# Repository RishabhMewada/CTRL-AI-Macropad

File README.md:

# CTRL-AI-Macropad

## What is CTRL?
CTRL is a custom-built Human-Computer Interaction (HCI) Development Board designed for productivity tooling, embedded experimentation, wireless HID systems, and future AI-assisted workflows.

Originally developed as a programmable macropad, the project has evolved into a battery-powered, dual-transport embedded platform built around the Raspberry Pi Pico (RP2040), featuring modular firmware architecture and wireless expansion capabilities.CTRL is a custom-built Human-Computer Interaction (HCI) Development Board designed for productivity tooling, embedded experimentation, wireless HID systems, and future AI-assisted workflows.

Originally developed as a programmable macropad, the project has evolved into a battery-powered, dual-transport embedded platform built around the Raspberry Pi Pico (RP2040), featuring modular firmware architecture and wireless expansion capabilities.
<p align="center">

-------------------------------------------------------------------------------------------------
## Purpose 
The goal of this project was to design a fully custom embedded input system from scratch — including:

- PCB design
- Multi-MCU system architecture
- Power management circuitry
- Firmware modularization
- Custom enclosure
- This project focuses on understanding:
- Embedded system design
- Hardware-software co-design
- Power-aware firmware
- Multi-transport communication (USB + BLE)
- Expandable interaction hardware

The system is built with future extensibility in mind rather than being limited to fixed macro execution.

-------------------------------------------------------------------------------------------------
## Features

*Core Hardware*

- 6 Mechanical Keys (Cherry MX compatible)
- Rotary Encoder with integrated push switch
- 1.14″ IPS SPI Display (ST7789)
- Raspberry Pi Pico (RP2040)
- BLE Co-Processor (UART interface)
- Li-ion battery support
- On-board charging IC
- Software-controlled power system
- Fully custom 2-layer PCB
- Expansion GPIO header
- SWD debug header
-------------------------------------------------------------------------------------------------
## Transport & Connectivity

- USB HID (via Raspberry Pi Pico)
- Bluetooth HID (via BLE co-processor)
- UART-based inter-MCU communication
- I²C sensor bus (IMU connected with interrupt support)
-------------------------------------------------------------------------------------------------
## Hardware
The PCB is designed using KiCad (open-source) and Fusion 360.

Specifications

- 2-layer PCB
- Diode-protected key matrix
- SPI-connected IPS display
- I²C IMU (interrupt-driven)
- UART-connected BLE module
- Li-ion battery charging circuit (MCP73831)
- 3.3V LDO regulator (AP2112K)
- Single USB-C interface (handled by Pico only)

All PCB source files are available in `/hardware/kicad`.

-------------------------------------------------------------------------------------------------

## Firmware
The firmware architecture has evolved from a monolithic USB HID mapping into a modular embedded system design.

**Architecture Overview**

*Subsystems include:*

- Input Processing Layer
- Power Management Layer
- Transport Abstraction Layer
- Communication Layer (UART BLE)
- Mode Manager

*Supported Features*

- Key matrix scanning
- Rotary encoder quadrature decoding
- USB HID output
- Bluetooth HID output
- 5-second long-press soft power
- Battery voltage monitoring
- Event-driven input routing

*Planned Enhancements*

- Dynamic key remapping
- On-device UI configuration
- BLE protocol expansion
- IMU gesture-based input
- Power optimization (sleep states)
- Desktop companion software

Firmware files are located in `/firmware`.

-------------------------------------------------------------------------------------------------
## Case
The enclosure is designed in Fusion 360 (personal use).
[STEP and source files are included in `/case`.]

**Dimensions:**
- Length: 11.8 cm
- Height: 6.3 cm
- Thickness: 1.5 cm

The enclosure is designed to be 3D printed.

~ **Recommended filament:** PLA  
PLA provides good dimensional accuracy, clean surface finish, and is easy to print, making it ideal for prototyping and desktop devices.

~ **Alternative:** PETG  
PETG can be used for improved durability and heat resistance, though it may require tuning for small cutouts.

[The enclosure is intended for indoor use and does not require high-temperature or impact-resistant materials.]

-------------------------------------------------------------------------------------------------
## Images

-------------------------------------------------------------------------------------------------

## Future AI Integration (Planned)
CTRL is designed to support AI-assisted workflows through a host-based companion application.
AI processing will run on the host computer, while CTRL serves as:

~ low-latency physical interface
~ status display device
~ context-aware shortcut controller

The hardware architecture is transport-agnostic, enabling flexible integration with higher-level software systems.

-------------------------------------------------------------------------------------------------
## BOM
The complete bill of materials (BOM), including purchase links, is available in  
`/hardware/bom.csv`.

Manufacturing & sourcing:
- PCB fabrication: **JLCPCB**
- Components (India): **Robu.in**
- Enclosure: Online 3D printing services
  
-------------------------------------------------------------------------------------------------
## License
This project is open-source hardware and software and is released under the **MIT License**.

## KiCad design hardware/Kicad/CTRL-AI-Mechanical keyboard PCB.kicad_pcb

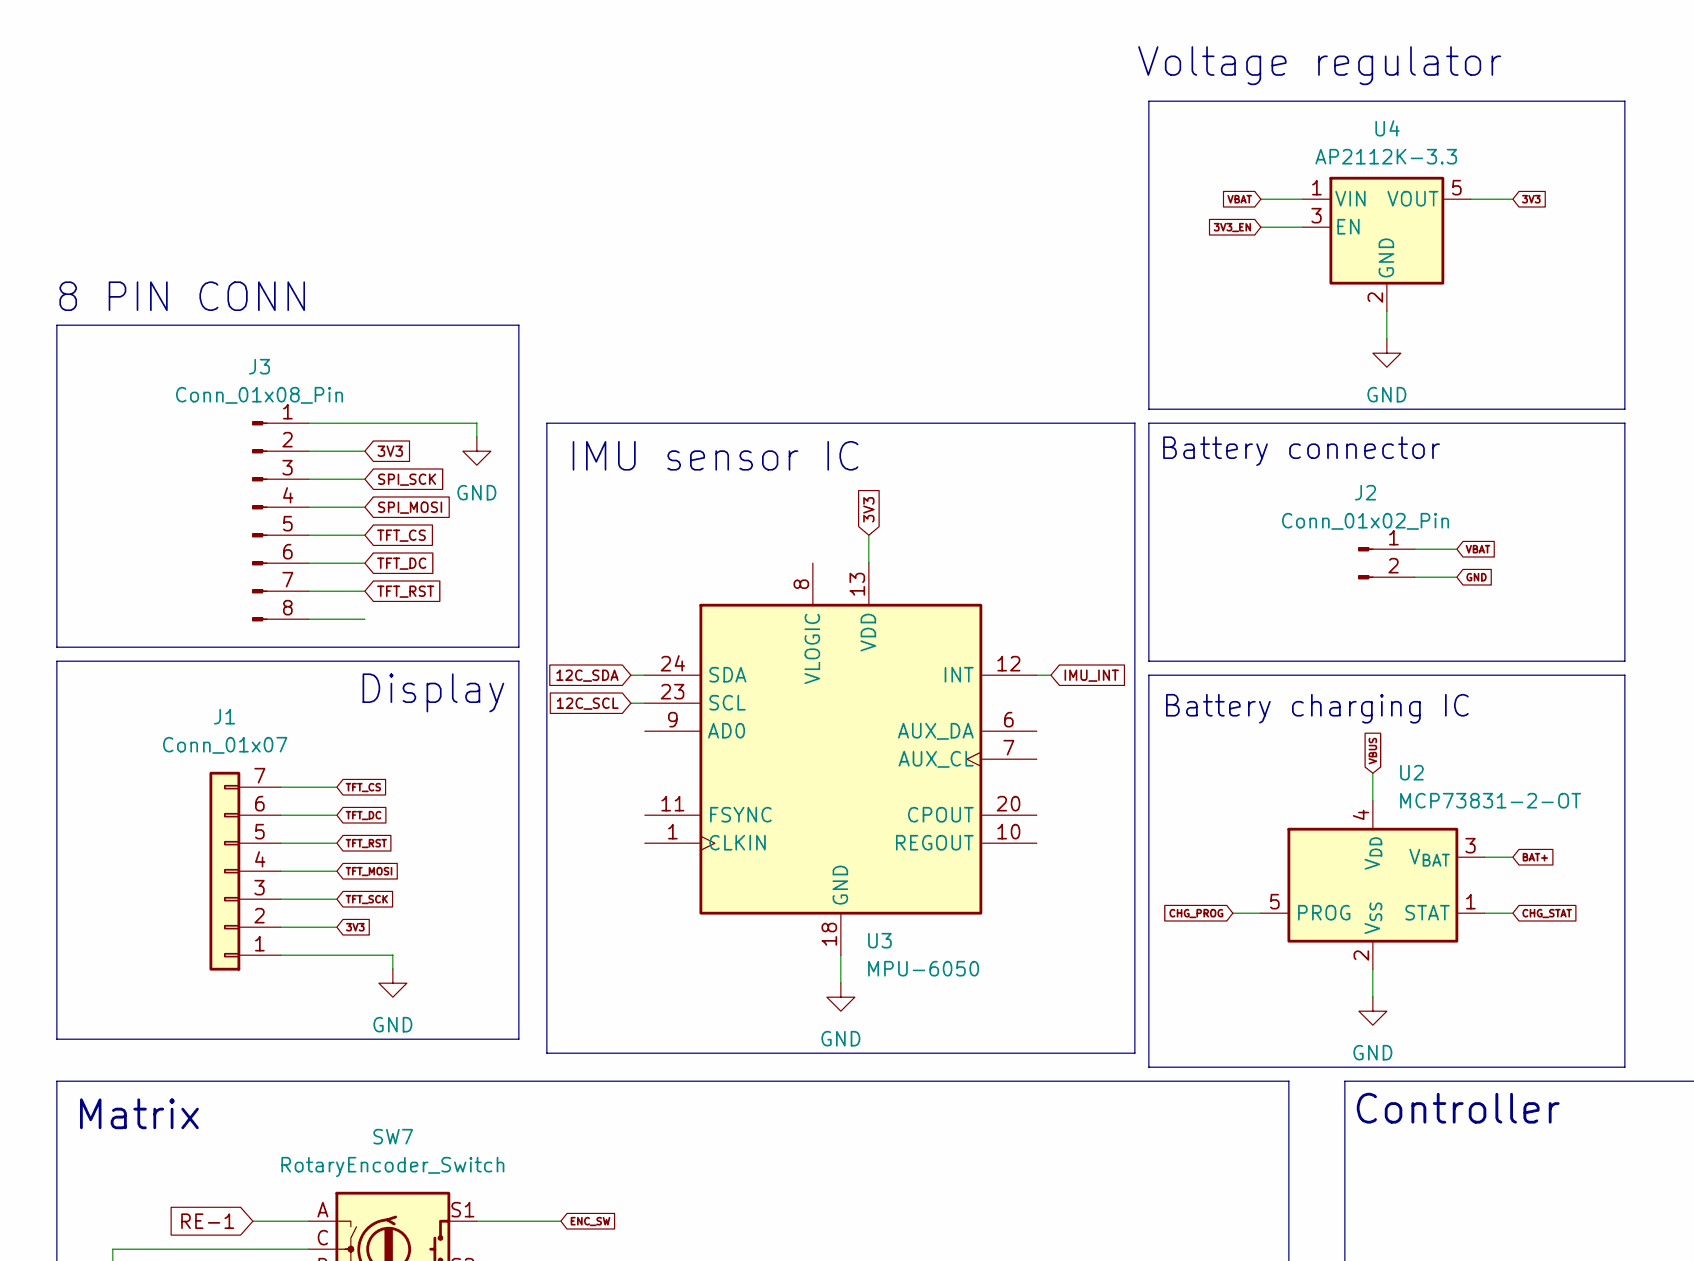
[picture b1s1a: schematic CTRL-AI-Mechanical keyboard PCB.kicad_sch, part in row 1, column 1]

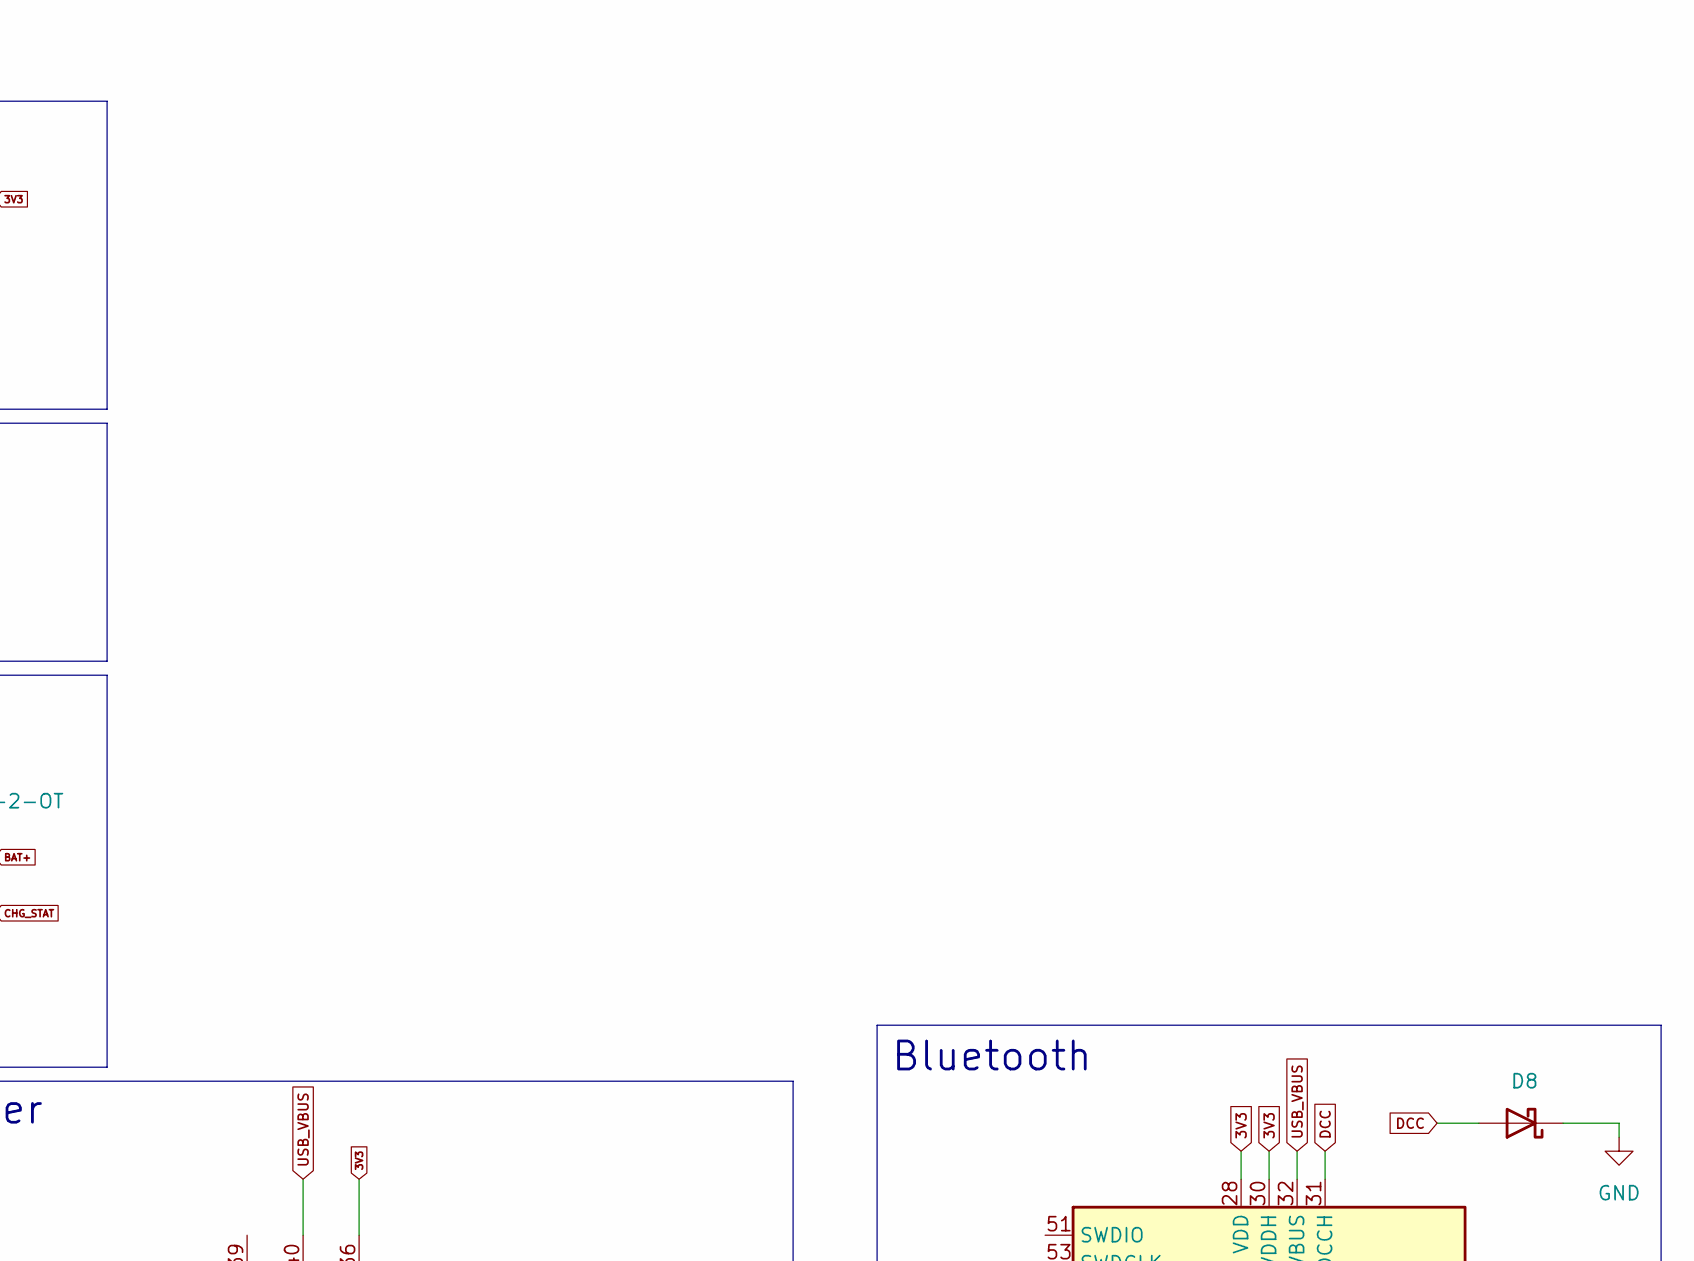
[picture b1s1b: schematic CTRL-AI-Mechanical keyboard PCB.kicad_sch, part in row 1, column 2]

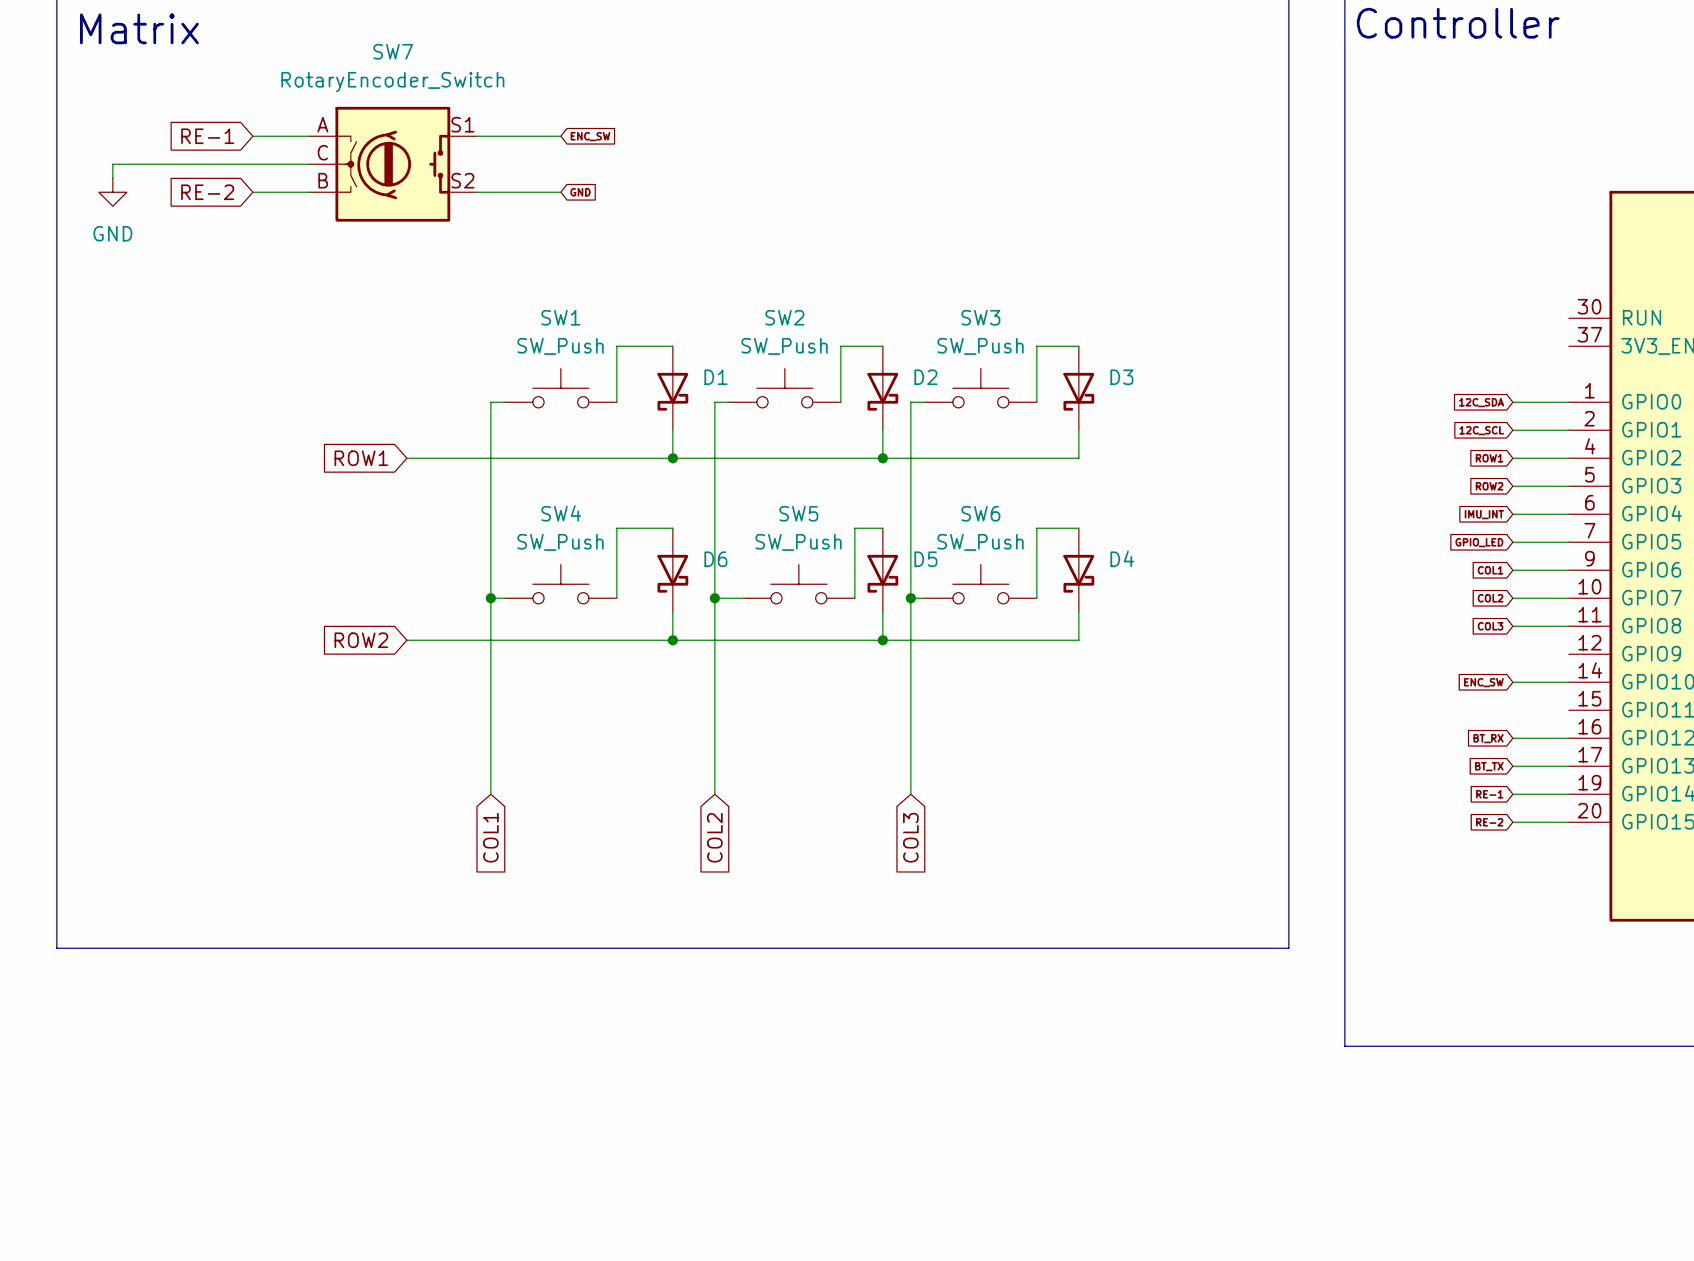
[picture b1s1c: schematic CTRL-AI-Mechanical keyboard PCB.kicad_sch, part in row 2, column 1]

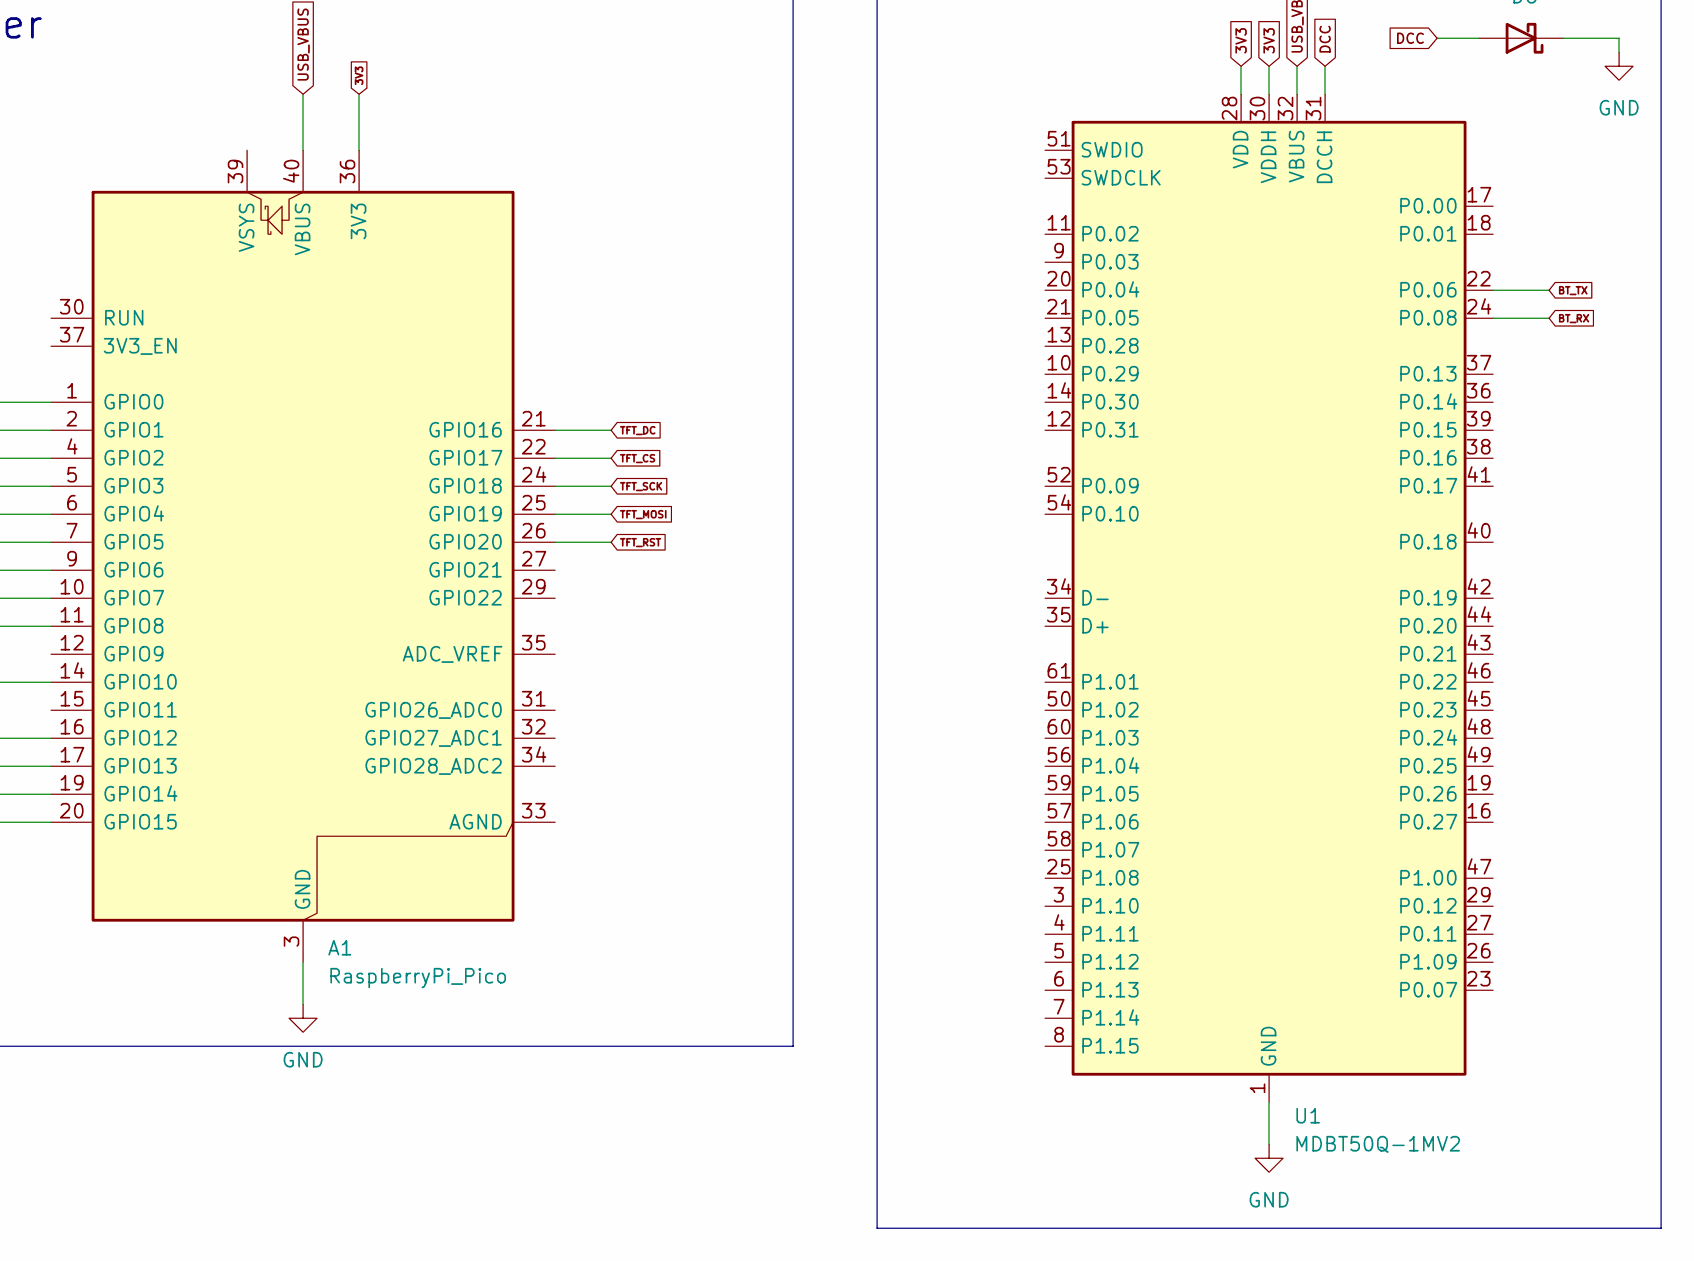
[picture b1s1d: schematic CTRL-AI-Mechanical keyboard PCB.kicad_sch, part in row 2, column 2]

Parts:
A1: RaspberryPi_Pico; RaspberryPi_Pico_Common_Unspecified
D1, D2, D3, D4, D5, D6, D8: DSB5712; D_DO-35_SOD27_P7.62mm_Horizontal
J1: Conn_01x07; PinHeader_1x07_P2.54mm_Vertical
J2: Conn_01x02_Pin; JST_PH_S2B-PH-K_1x02_P2.00mm_Horizontal
J3: Conn_01x08_Pin; PinHeader_1x07_P2.54mm_Horizontal
SW1, SW2, SW3, SW4, SW5, SW6: SW_Push; SW_Cherry_MX_1.00u_PCB
SW7: RotaryEncoder_Switch; RotaryEncoder_Alps_EC11E-Switch_Vertical_H20mm
U1: MDBT50Q-1MV2; Raytac_MDBT50Q
U2: MCP73831-2-OT; SOT-23-5
U3: MPU-6050; InvenSense_QFN-24_4x4mm_P0.5mm
U4: AP2112K-3.3; SOT-23-5

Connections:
3V3: A1.36 (3V3), J1.2, J3.2, U1.28 (VDD), U1.30 (VDDH), U3.13 (VDD), U4.5 (VOUT)
3V3_EN: U4.3 (EN)
12C_SCL: A1.2 (GPIO1), U3.23 (SCL)
12C_SDA: A1.1 (GPIO0), U3.24 (SDA)
BAT+: U2.3 (V_{BAT})
BT_RX: A1.16 (GPIO12), U1.24 (P0.08)
BT_TX: A1.17 (GPIO13), U1.22 (P0.06)
CHG_PROG: U2.5 (PROG)
CHG_STAT: U2.1 (STAT)
COL1: A1.9 (GPIO6), SW1.1, SW4.1
COL2: A1.10 (GPIO7), SW2.1, SW5.1
COL3: A1.11 (GPIO8), SW3.1, SW6.1
DCC: D8.2 (A), U1.31 (DCCH)
ENC_SW: A1.14 (GPIO10), SW7.S1
GND: A1.3 (GND), A1.8 (GND), A1.13 (GND), A1.18 (GND), A1.23 (GND), A1.28 (GND), A1.38 (GND), D8.1 (K), J1.1, J2.2, J3.1, SW7.C, SW7.S2, U1.1 (GND), U1.2 (GND), U1.15 (GND), U1.33 (GND), U1.55 (GND), U2.2 (V_{SS}), U3.18 (GND), U4.2 (GND)
GPIO_LED: A1.7 (GPIO5)
IMU_INT: A1.6 (GPIO4), U3.12 (INT)
unnamed: D1.2 (A), SW1.2
unnamed: D2.2 (A), SW2.2
unnamed: D3.2 (A), SW3.2
unnamed: D4.2 (A), SW6.2
unnamed: D5.2 (A), SW5.2
unnamed: D6.2 (A), SW4.2
RE-1: A1.19 (GPIO14), SW7.A
RE-2: A1.20 (GPIO15), SW7.B
ROW1: A1.4 (GPIO2), D1.1 (K), D2.1 (K), D3.1 (K)
ROW2: A1.5 (GPIO3), D4.1 (K), D5.1 (K), D6.1 (K)
SPI_MOSI: J3.4
SPI_SCK: J3.3
TFT_CS: A1.22 (GPIO17), J1.7, J3.5
TFT_DC: A1.21 (GPIO16), J1.6, J3.6
TFT_MOSI: A1.25 (GPIO19), J1.4
TFT_RST: A1.26 (GPIO20), J1.5, J3.7
TFT_SCK: A1.24 (GPIO18), J1.3
USB_VBUS: A1.40 (VBUS), U1.32 (VBUS)
VBAT: J2.1, U4.1 (VIN)
VBUS: U2.4 (V_{DD})

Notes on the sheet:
Battery connector
Voltage regulator
Battery charging IC
Display
Bluetooth
Matrix
8 PIN CONN
Controller
IMU sensor IC

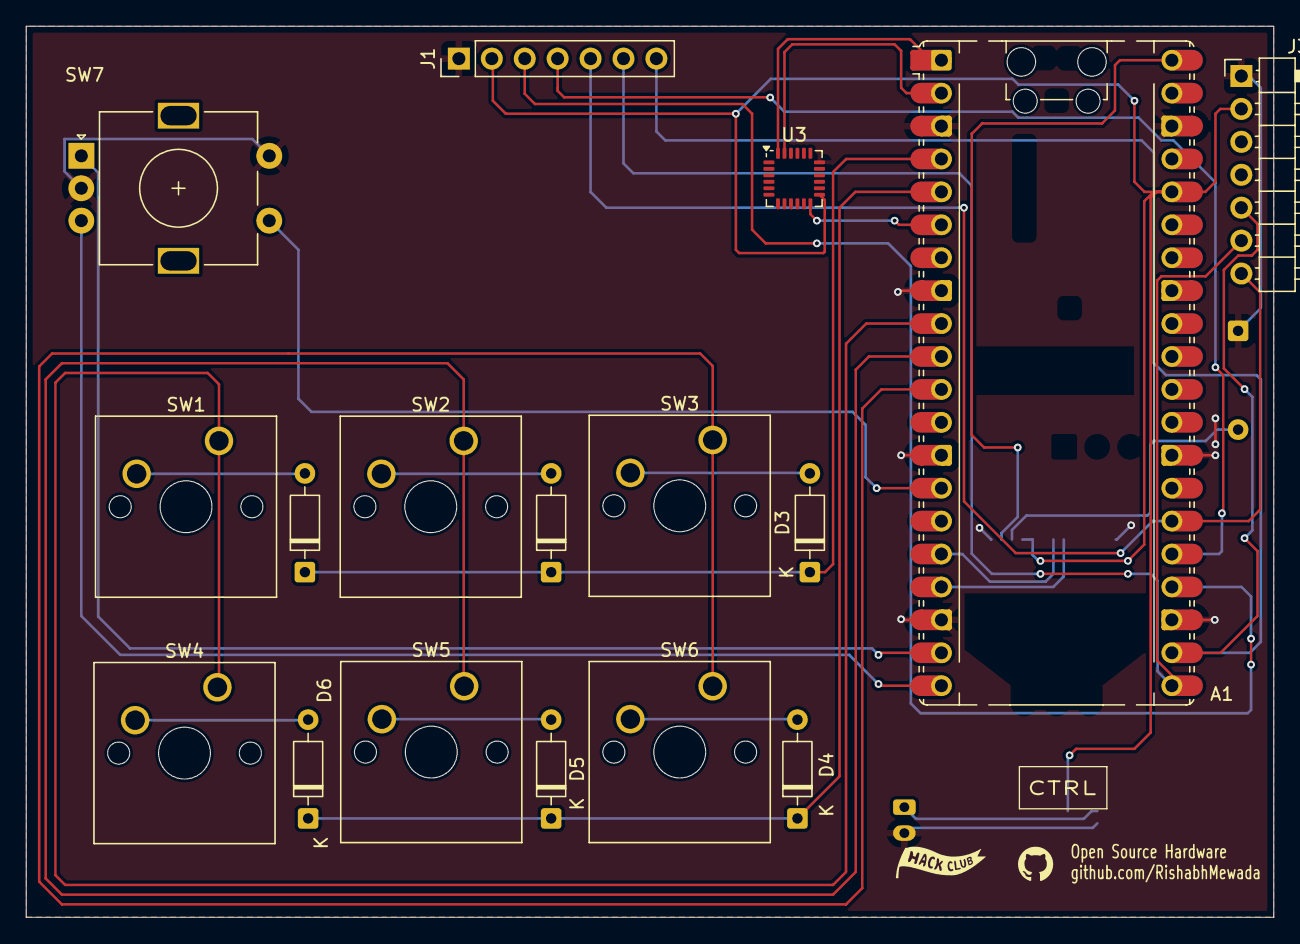
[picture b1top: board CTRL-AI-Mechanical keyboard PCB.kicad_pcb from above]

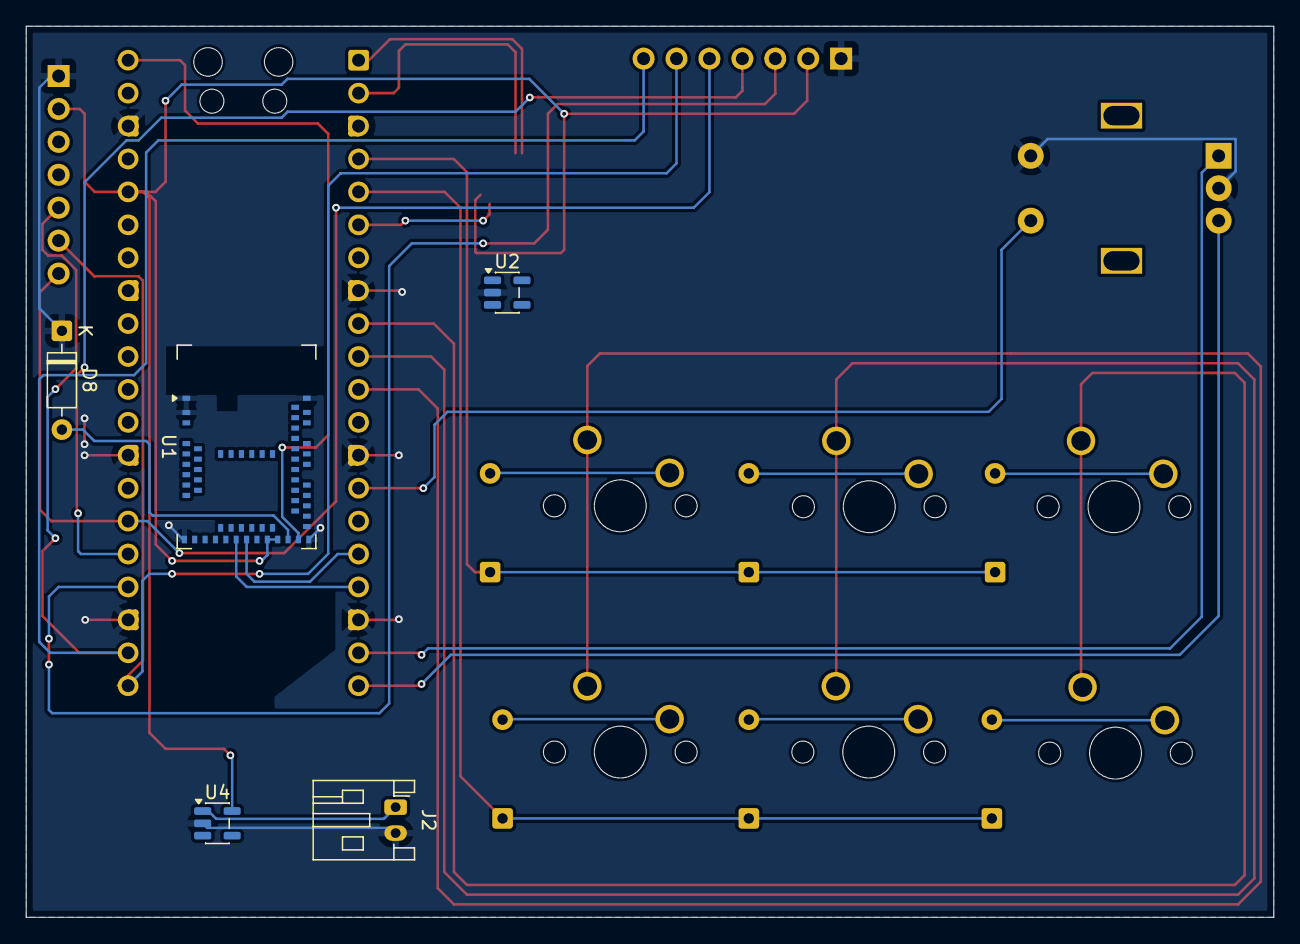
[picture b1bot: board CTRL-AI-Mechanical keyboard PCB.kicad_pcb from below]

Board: 2 copper layers, 96.2 x 68.8 mm, 22 parts (5 on the bottom side), 29 nets.

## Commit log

2025-12-28 Create assets
2026-01-12 Add version info for v1.0 release
    Added version information for the initial release.
2026-03-01 Revise README for improved project documentation
    Updated the README to enhance clarity and detail about the CTRL-AI-Macropad project, including features, firmware architecture, and future AI integration.
